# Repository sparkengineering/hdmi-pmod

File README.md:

# hdmi-pmod

## Description

HDMI type A receptacle to Digilent Pmod™ breakout board.

- Impedance matched & length tuned differential lines
- Includes 3.3V to 5V boost converter (max. 200mA)
- Pinout to match Digilent high-speed Pmod™ e.g. on Arty A7
- Tested with Arty A7 board at 1280x720 @ 60HZ

## Contents

| File                                         | Description             |
|----------------------------------------------|-------------------------|
| [hdmi-pmod.pdf](./hdmi-pmod.pdf)             | Schematic in PDF format |
| [hdmi-pmod.csv](./hdmi-pmod.csv)             | BOM in CSV format       |
| [hdmi-pmod.png](./hdmi-pmod.png)             | PCB 3D render           |
|                                              |                         |
| [hdmi-pmod.kicad_pro](./hdmi-pmod.kicad_pro) | KiCad 8.0.2 project     |
| [hdmi-pmod.kicad_pcb](./hdmi-pmod.kicad_pcb) | KiCad 8.0.2 PCB         |
| [hdmi-pmod.kicad_sch](./hdmi-pmod.kicad_sch) | KiCad 8.0.2 schematic   |

## Further Reading

- FPGA display controller with support for VGA, DVI, and HDMI [^1]
- Digital Visual Interface Specification Version 1.0 [^2]
- BML DVI digital video for FPGAs over PMOD [^3]
- fpga4fun.com HDMI [^4]
- Hackaday.io HDMI PMOD [^5]

[^1]: https://github.com/projf/display_controller
[^2]: https://glenwing.github.io/docs/DVI-1.0.pdf
[^3]: https://blackmesalabs.wordpress.com/2017/12/15/bml-hdmi-video-for-fpgas-over-pmod/
[^4]: https://www.fpga4fun.com/HDMI.html
[^5]: https://hackaday.io/project/176327-hdmi-pmod

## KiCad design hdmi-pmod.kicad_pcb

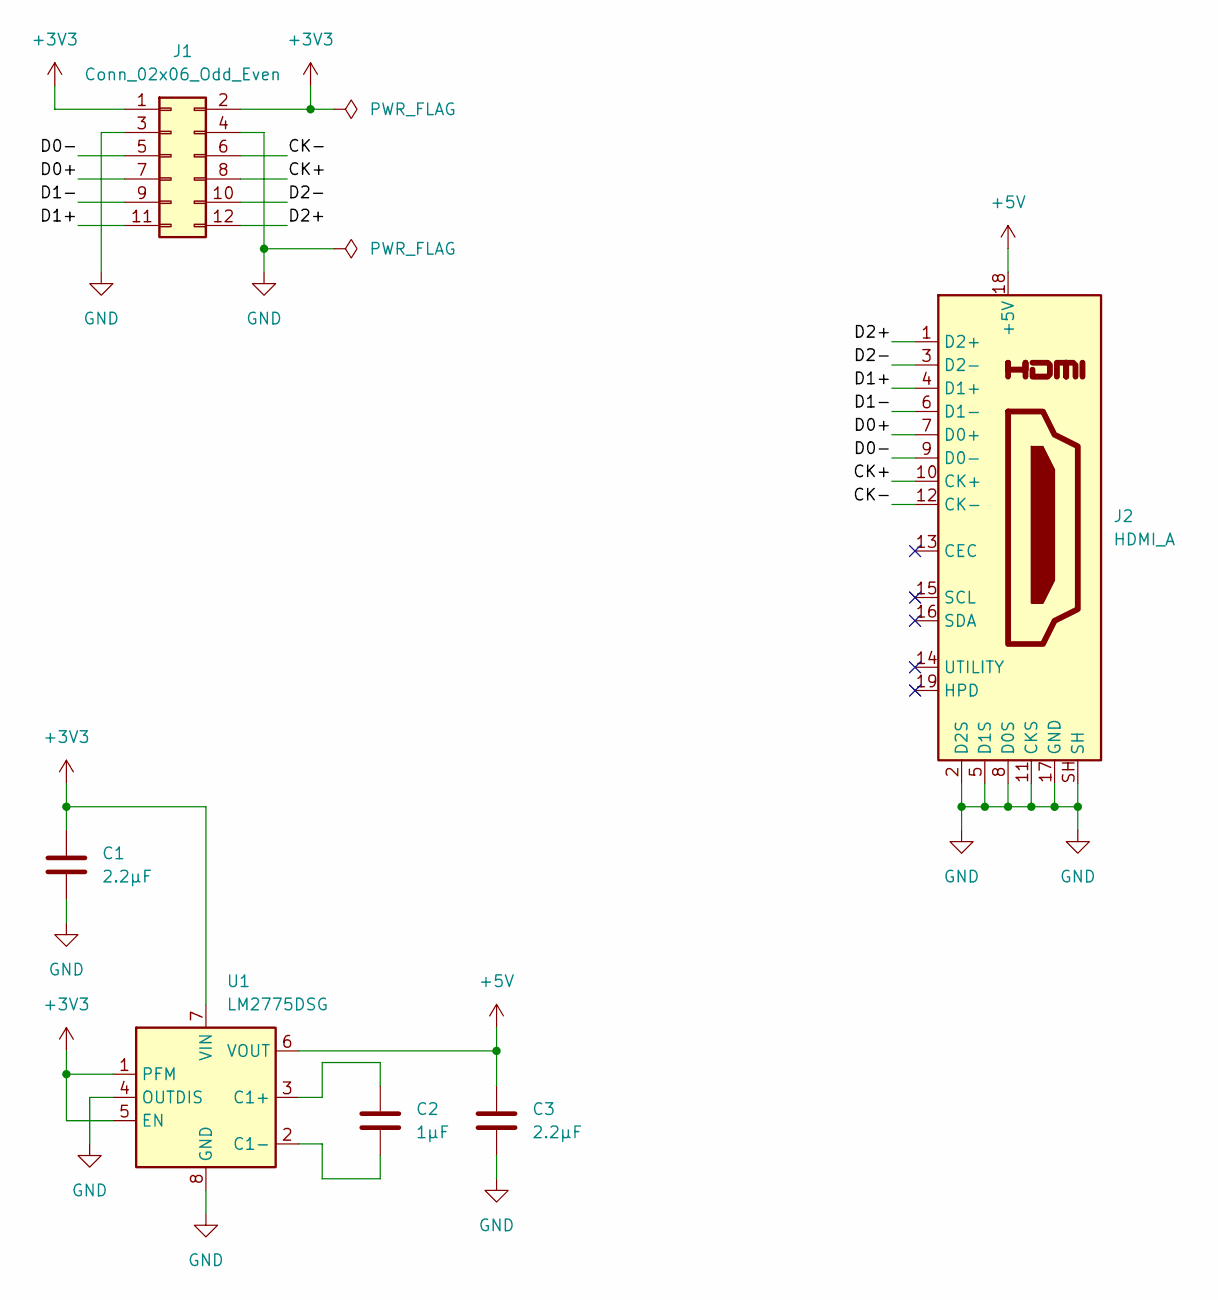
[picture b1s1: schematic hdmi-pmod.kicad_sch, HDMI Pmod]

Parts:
C1, C3: 2.2µF; C_0402_1005Metric; MPN GRM155R61C225KE11D
C2: 1µF; C_0402_1005Metric; MPN GRM155R61C105KA12D
J1: Conn_02x06_Odd_Even; PinHeader_2x06_P2.54mm_Horizontal; MPN 826634-6
J2: HDMI_A; HDMI_A_Molex_208658-1001_Horizontal; MPN 208658-1001
U1: LM2775DSG; WSON-8-1EP_2x2mm_P0.5mm_EP0.9x1.6mm; MPN LM2775DSGT

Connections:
+3V3: C1.1, J1.1, J1.2, U1.1 (PFM), U1.5 (EN), U1.7 (VIN)
+5V: C3.1, J2.18 (+5V), U1.6 (VOUT)
/CK+: J1.8, J2.10 (CK+)
/CK-: J1.6, J2.12 (CK-)
/D0+: J1.7, J2.7 (D0+)
/D0-: J1.5, J2.9 (D0-)
/D1+: J1.11, J2.4 (D1+)
/D1-: J1.9, J2.6 (D1-)
/D2+: J1.12, J2.1 (D2+)
/D2-: J1.10, J2.3 (D2-)
GND: C1.2, C3.2, J1.3, J1.4, J2.2 (D2S), J2.5 (D1S), J2.8 (D0S), J2.11 (CKS), J2.17 (GND), J2.SH, U1.4 (OUTDIS), U1.8 (GND), U1.9 (GND)
unnamed: C2.1, U1.3 (C1+)
unnamed: C2.2, U1.2 (C1-)

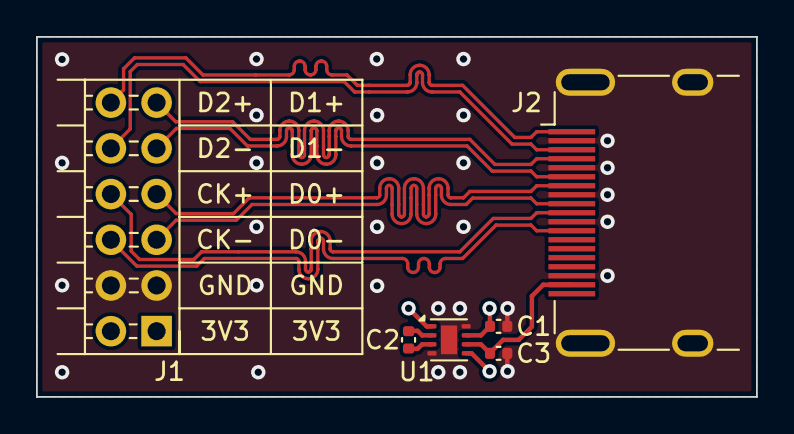
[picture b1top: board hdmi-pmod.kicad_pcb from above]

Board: 4 copper layers, 40.0 x 20.0 mm, 6 parts (0 on the bottom side), 13 nets.

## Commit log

2024-02-29 Update README.md
    Add AISLER and KiCanvas shields
2024-02-29 Update README.md
    Add some further reading
2024-03-21 Update symbols, fix ERC
2024-03-23 Add kicad-action ERC/DRC checks
2024-03-23 Update main.yml
    Maybe fix artifact upload?
2024-05-19 Add revision v1.1
    Update symbols, footprints, etc. for KiCad 8.0.2
    Remove custom bridges to remove DRC errors
    Increment revision number
2024-05-19 Bump kicad-action workflow version
2024-05-19 Waive remaining silkscreen DRC violations
2024-05-19 Add ERC/DRC workflow badge to README.md
